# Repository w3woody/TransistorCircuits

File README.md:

# TransistorCircuits

Circuit board designs for the "Introduction to Digital Computers" series.

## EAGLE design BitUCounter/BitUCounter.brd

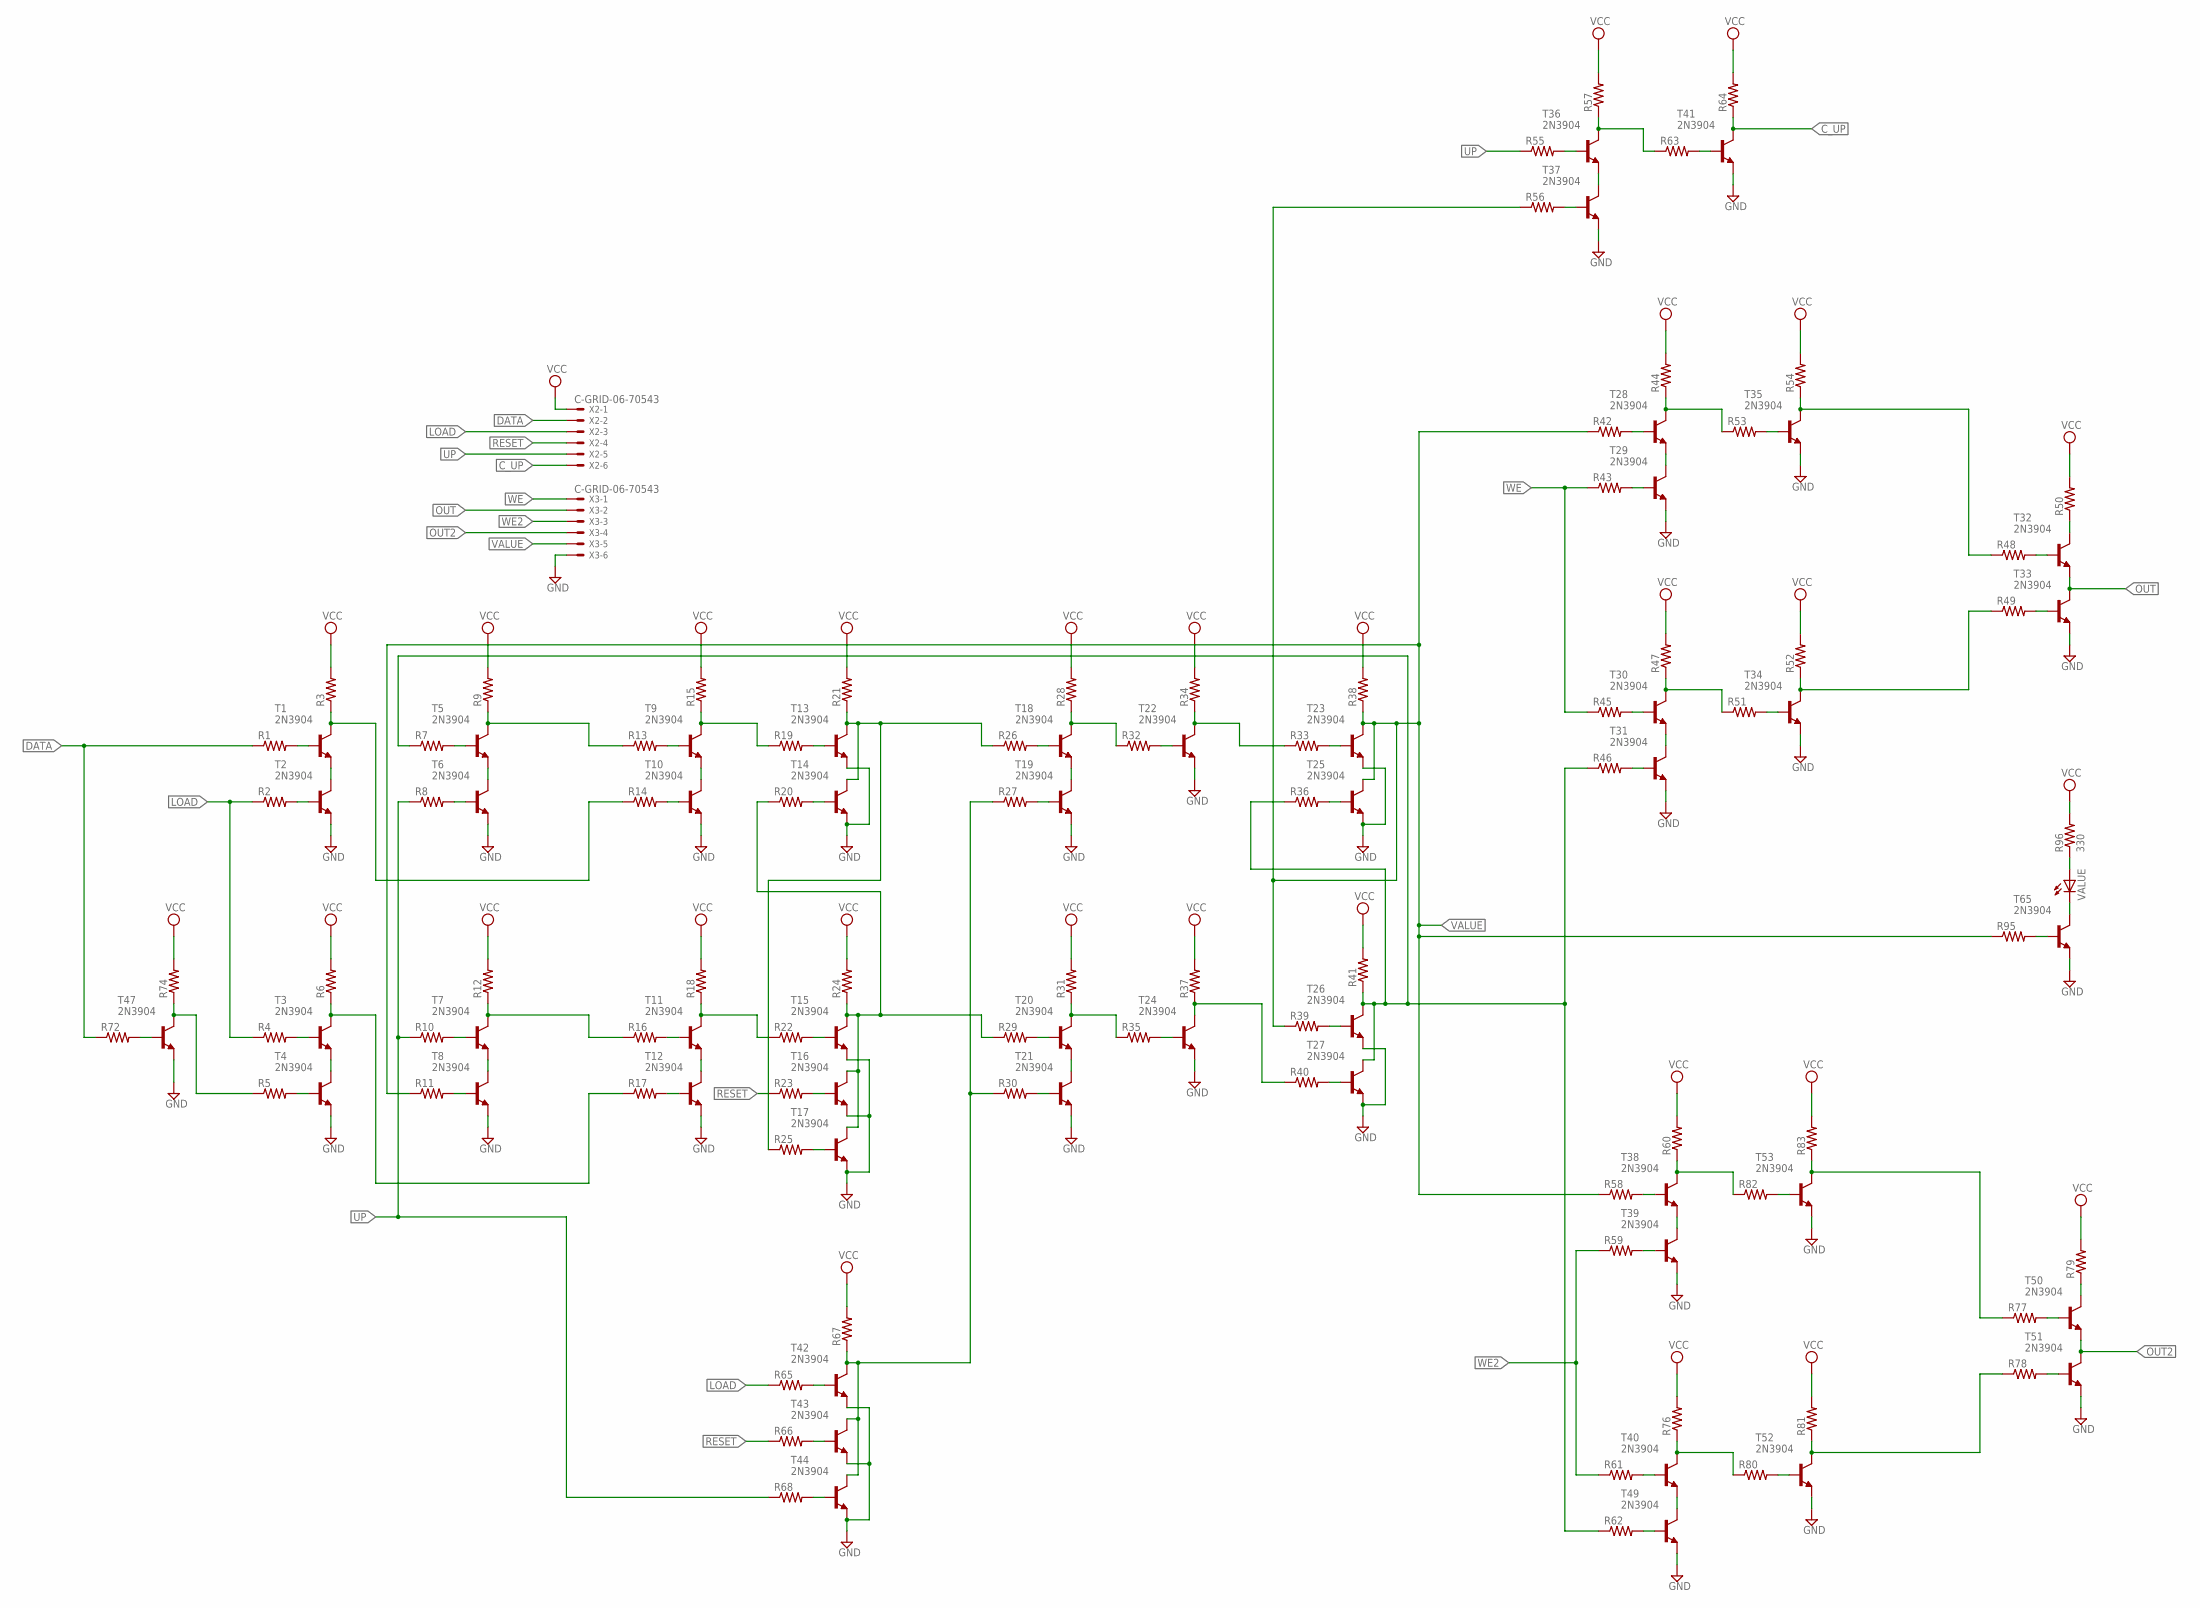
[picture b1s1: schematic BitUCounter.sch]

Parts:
R1, R2, R3, R4, R5, R6, R7, R8, R9, R10, R11, R12, R13, R14, R15, R16, R17, R18, R19, R20, R21, R22, R23, R24, R25, R26, R27, R28, R29, R30, R31, R32, R33, R34, R35, R36, R37, R38, R39, R40, R41, R42, R43, R44, R45, R46, R47, R48, R49, R50, R51, R52, R53, R54, R55, R56, R57, R58, R59, R60, R61, R62, R63, R64, R65, R66, R67, R68, R72, R74, R76, R77, R78, R79, R80, R81, R82, R83, R95: R-US_0309/10; 0309/10
R96: 330; 0309/10
T1, T2, T3, T4, T5, T6, T7, T8, T9, T10, T11, T12, T13, T14, T15, T16, T17, T18, T19, T20, T21, T22, T23, T24, T25, T26, T27, T28, T29, T30, T31, T32, T33, T34, T35, T36, T37, T38, T39, T40, T41, T42, T43, T44, T47, T49, T50, T51, T52, T53, T65: 2N3904; TO92
VALUE: LED5MM
X2, X3: C-GRID-06-70543; 70543-06

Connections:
C_UP: R64.1, T41.1 (C), X2.6
DATA: R1.1, R72.1, X2.2
GND: T2.3 (E), T4.3 (E), T6.3 (E), T8.3 (E), T10.3 (E), T12.3 (E), T13.3 (E), T14.3 (E), T15.3 (E), T16.3 (E), T17.3 (E), T19.3 (E), T21.3 (E), T22.3 (E), T23.3 (E), T24.3 (E), T25.3 (E), T26.3 (E), T27.3 (E), T29.3 (E), T31.3 (E), T33.3 (E), T34.3 (E), T35.3 (E), T37.3 (E), T39.3 (E), T41.3 (E), T42.3 (E), T43.3 (E), T44.3 (E), T47.3 (E), T49.3 (E), T51.3 (E), T52.3 (E), T53.3 (E), T65.3 (E), X3.6
LOAD: R2.1, R4.1, R65.1, X2.3
unnamed: R5.1, R74.1, T47.1 (C)
unnamed: R72.2, T47.2 (B)
unnamed: R7.1, R36.1, R41.1, R46.1, R62.1, T26.1 (C), T27.1 (C)
unnamed: R6.1, R17.1, T3.1 (C)
unnamed: T3.3 (E), T4.1 (C)
unnamed: R5.2, T4.2 (B)
unnamed: R4.2, T3.2 (B)
unnamed: R2.2, T2.2 (B)
unnamed: R1.2, T1.2 (B)
unnamed: T1.3 (E), T2.1 (C)
unnamed: R3.1, R14.1, T1.1 (C)
unnamed: R9.1, R13.1, T5.1 (C)
unnamed: R7.2, T5.2 (B)
unnamed: R8.2, T6.2 (B)
unnamed: T5.3 (E), T6.1 (C)
unnamed: R12.1, R16.1, T7.1 (C)
unnamed: R10.2, T7.2 (B)
unnamed: R11.2, T8.2 (B)
unnamed: T7.3 (E), T8.1 (C)
unnamed: R18.1, R22.1, T11.1 (C)
unnamed: R16.2, T11.2 (B)
unnamed: R17.2, T12.2 (B)
unnamed: T11.3 (E), T12.1 (C)
unnamed: R14.2, T10.2 (B)
unnamed: T9.3 (E), T10.1 (C)
unnamed: R15.1, R19.1, T9.1 (C)
unnamed: R13.2, T9.2 (B)
unnamed: R21.1, R25.1, R26.1, T13.1 (C), T14.1 (C)
unnamed: R58.2, T38.2 (B)
unnamed: R19.2, T13.2 (B)
unnamed: R20.2, T14.2 (B)
unnamed: R20.1, R24.1, R29.1, T15.1 (C), T16.1 (C), T17.1 (C)
unnamed: R59.2, T39.2 (B)
unnamed: T38.3 (E), T39.1 (C)
unnamed: R22.2, T15.2 (B)
unnamed: R23.2, T16.2 (B)
unnamed: R25.2, T17.2 (B)
unnamed: R30.2, T21.2 (B)
unnamed: T20.3 (E), T21.1 (C)
unnamed: R31.1, R35.1, T20.1 (C)
unnamed: R29.2, T20.2 (B)
unnamed: R35.2, T24.2 (B)
unnamed: R60.1, R82.1, T38.1 (C)
unnamed: R26.2, T18.2 (B)
unnamed: R27.2, T19.2 (B)
unnamed: T18.3 (E), T19.1 (C)
unnamed: R28.1, R32.1, T18.1 (C)
unnamed: R32.2, T22.2 (B)
unnamed: R33.1, R34.1, T22.1 (C)
unnamed: R82.2, T53.2 (B)
unnamed: R77.1, R83.1, T53.1 (C)
unnamed: R78.1, R81.1, T52.1 (C)
unnamed: R36.2, T25.2 (B)
unnamed: R33.2, T23.2 (B)
unnamed: R80.2, T52.2 (B)
unnamed: R39.2, T26.2 (B)
unnamed: R40.2, T27.2 (B)
unnamed: R42.2, T28.2 (B)
unnamed: R43.2, T29.2 (B)
unnamed: T28.3 (E), T29.1 (C)
unnamed: R44.1, R53.1, T28.1 (C)
unnamed: R53.2, T35.2 (B)
unnamed: R48.1, R54.1, T35.1 (C)
unnamed: R49.1, R52.1, T34.1 (C)
unnamed: R51.2, T34.2 (B)
unnamed: R47.1, R51.1, T30.1 (C)
unnamed: T30.3 (E), T31.1 (C)
unnamed: R46.2, T31.2 (B)
unnamed: R45.2, T30.2 (B)
unnamed: R48.2, T32.2 (B)
unnamed: R50.1, T32.1 (C)
unnamed: R76.1, R80.1, T40.1 (C)
unnamed: R49.2, T33.2 (B)
unnamed: T40.3 (E), T49.1 (C)
unnamed: R62.2, T49.2 (B)
unnamed: R61.2, T40.2 (B)
unnamed: R77.2, T50.2 (B)
unnamed: R57.1, R63.1, T36.1 (C)
unnamed: T36.3 (E), T37.1 (C)
unnamed: R56.2, T37.2 (B)
unnamed: R55.2, T36.2 (B)
unnamed: R79.1, T50.1 (C)
unnamed: R63.2, T41.2 (B)
unnamed: R78.2, T51.2 (B)
unnamed: R65.2, T42.2 (B)
unnamed: R66.2, T43.2 (B)
unnamed: R68.2, T44.2 (B)
unnamed: R27.1, R30.1, R67.1, T42.1 (C), T43.1 (C), T44.1 (C)
unnamed: R37.1, R40.1, T24.1 (C)
unnamed: R96.1, VALUE.A
unnamed: R95.2, T65.2 (B)
unnamed: T65.1 (C), VALUE.K (C)
OUT: T32.3 (E), T33.1 (C), X3.2
OUT2: T50.3 (E), T51.1 (C), X3.4
RESET: R23.1, R66.1, X2.4
UP: R8.1, R10.1, R55.1, R68.1, X2.5
VALUE: R11.1, R38.1, R39.1, R42.1, R56.1, R58.1, R95.1, T23.1 (C), T25.1 (C), X3.5
VCC: R3.2, R6.2, R9.2, R12.2, R15.2, R18.2, R21.2, R24.2, R28.2, R31.2, R34.2, R37.2, R38.2, R41.2, R44.2, R47.2, R50.2, R52.2, R54.2, R57.2, R60.2, R64.2, R67.2, R74.2, R76.2, R79.2, R81.2, R83.2, R96.2, X2.1
WE: R43.1, R45.1, X3.1
WE2: R59.1, R61.1, X3.3

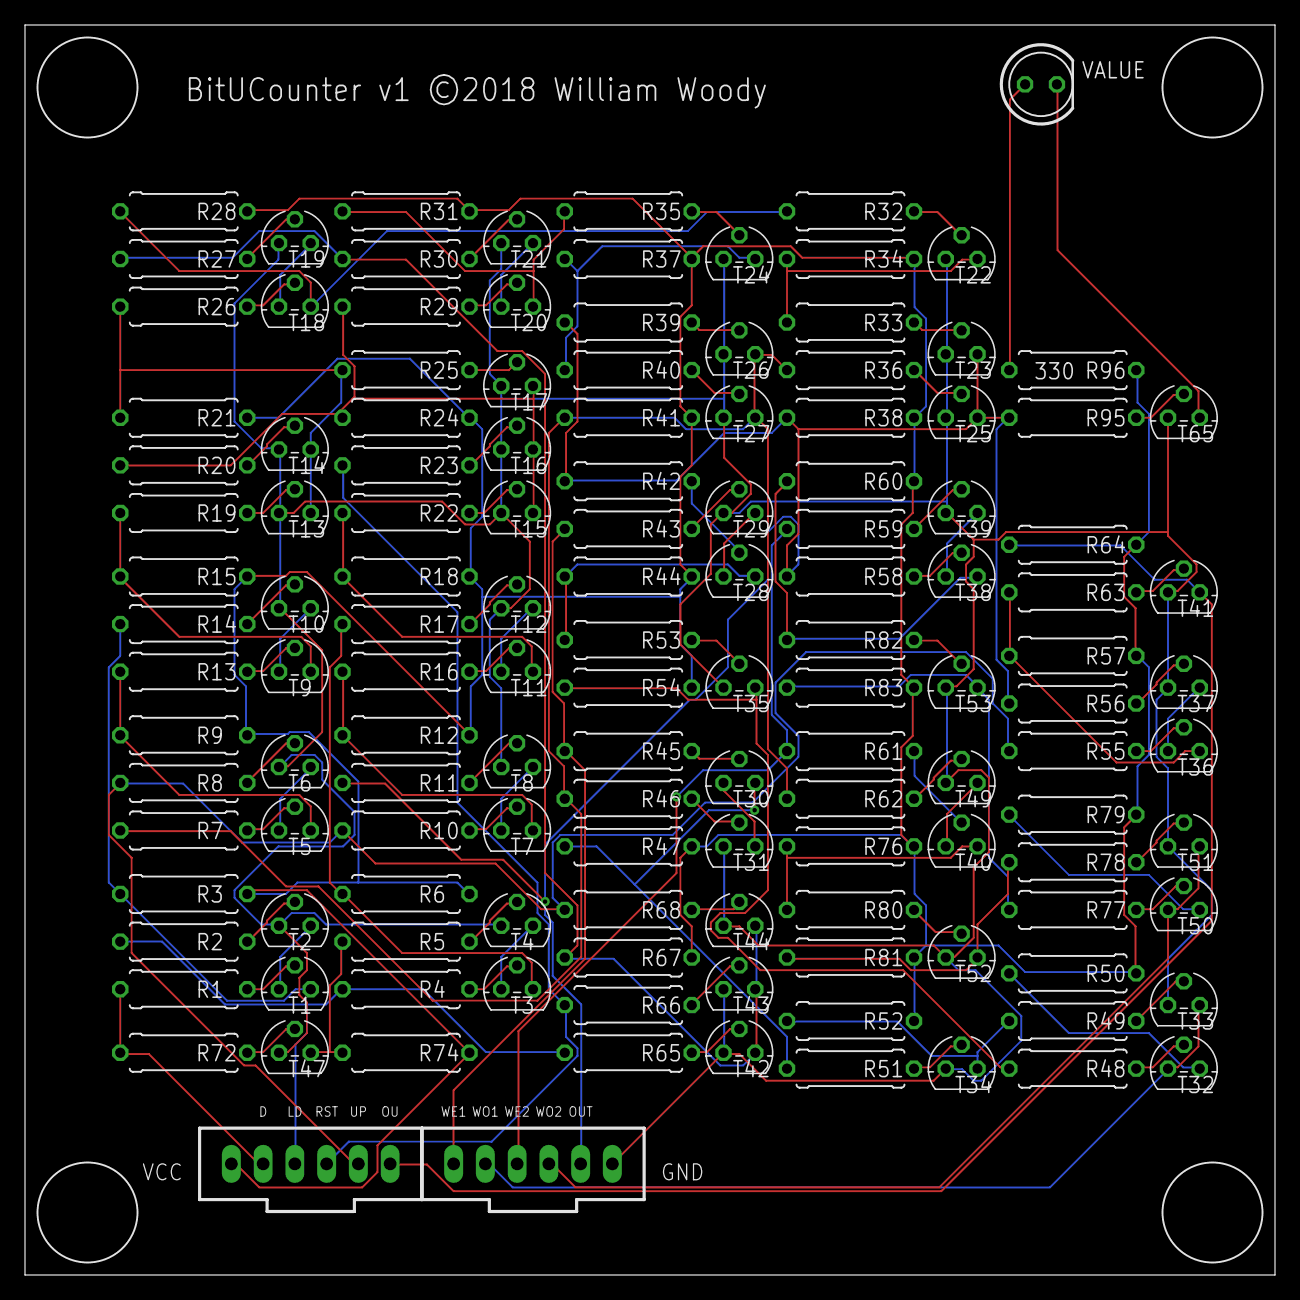
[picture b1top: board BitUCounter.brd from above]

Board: 2 copper layers, 100.0 x 100.0 mm, 134 parts (0 on the bottom side), 104 nets.

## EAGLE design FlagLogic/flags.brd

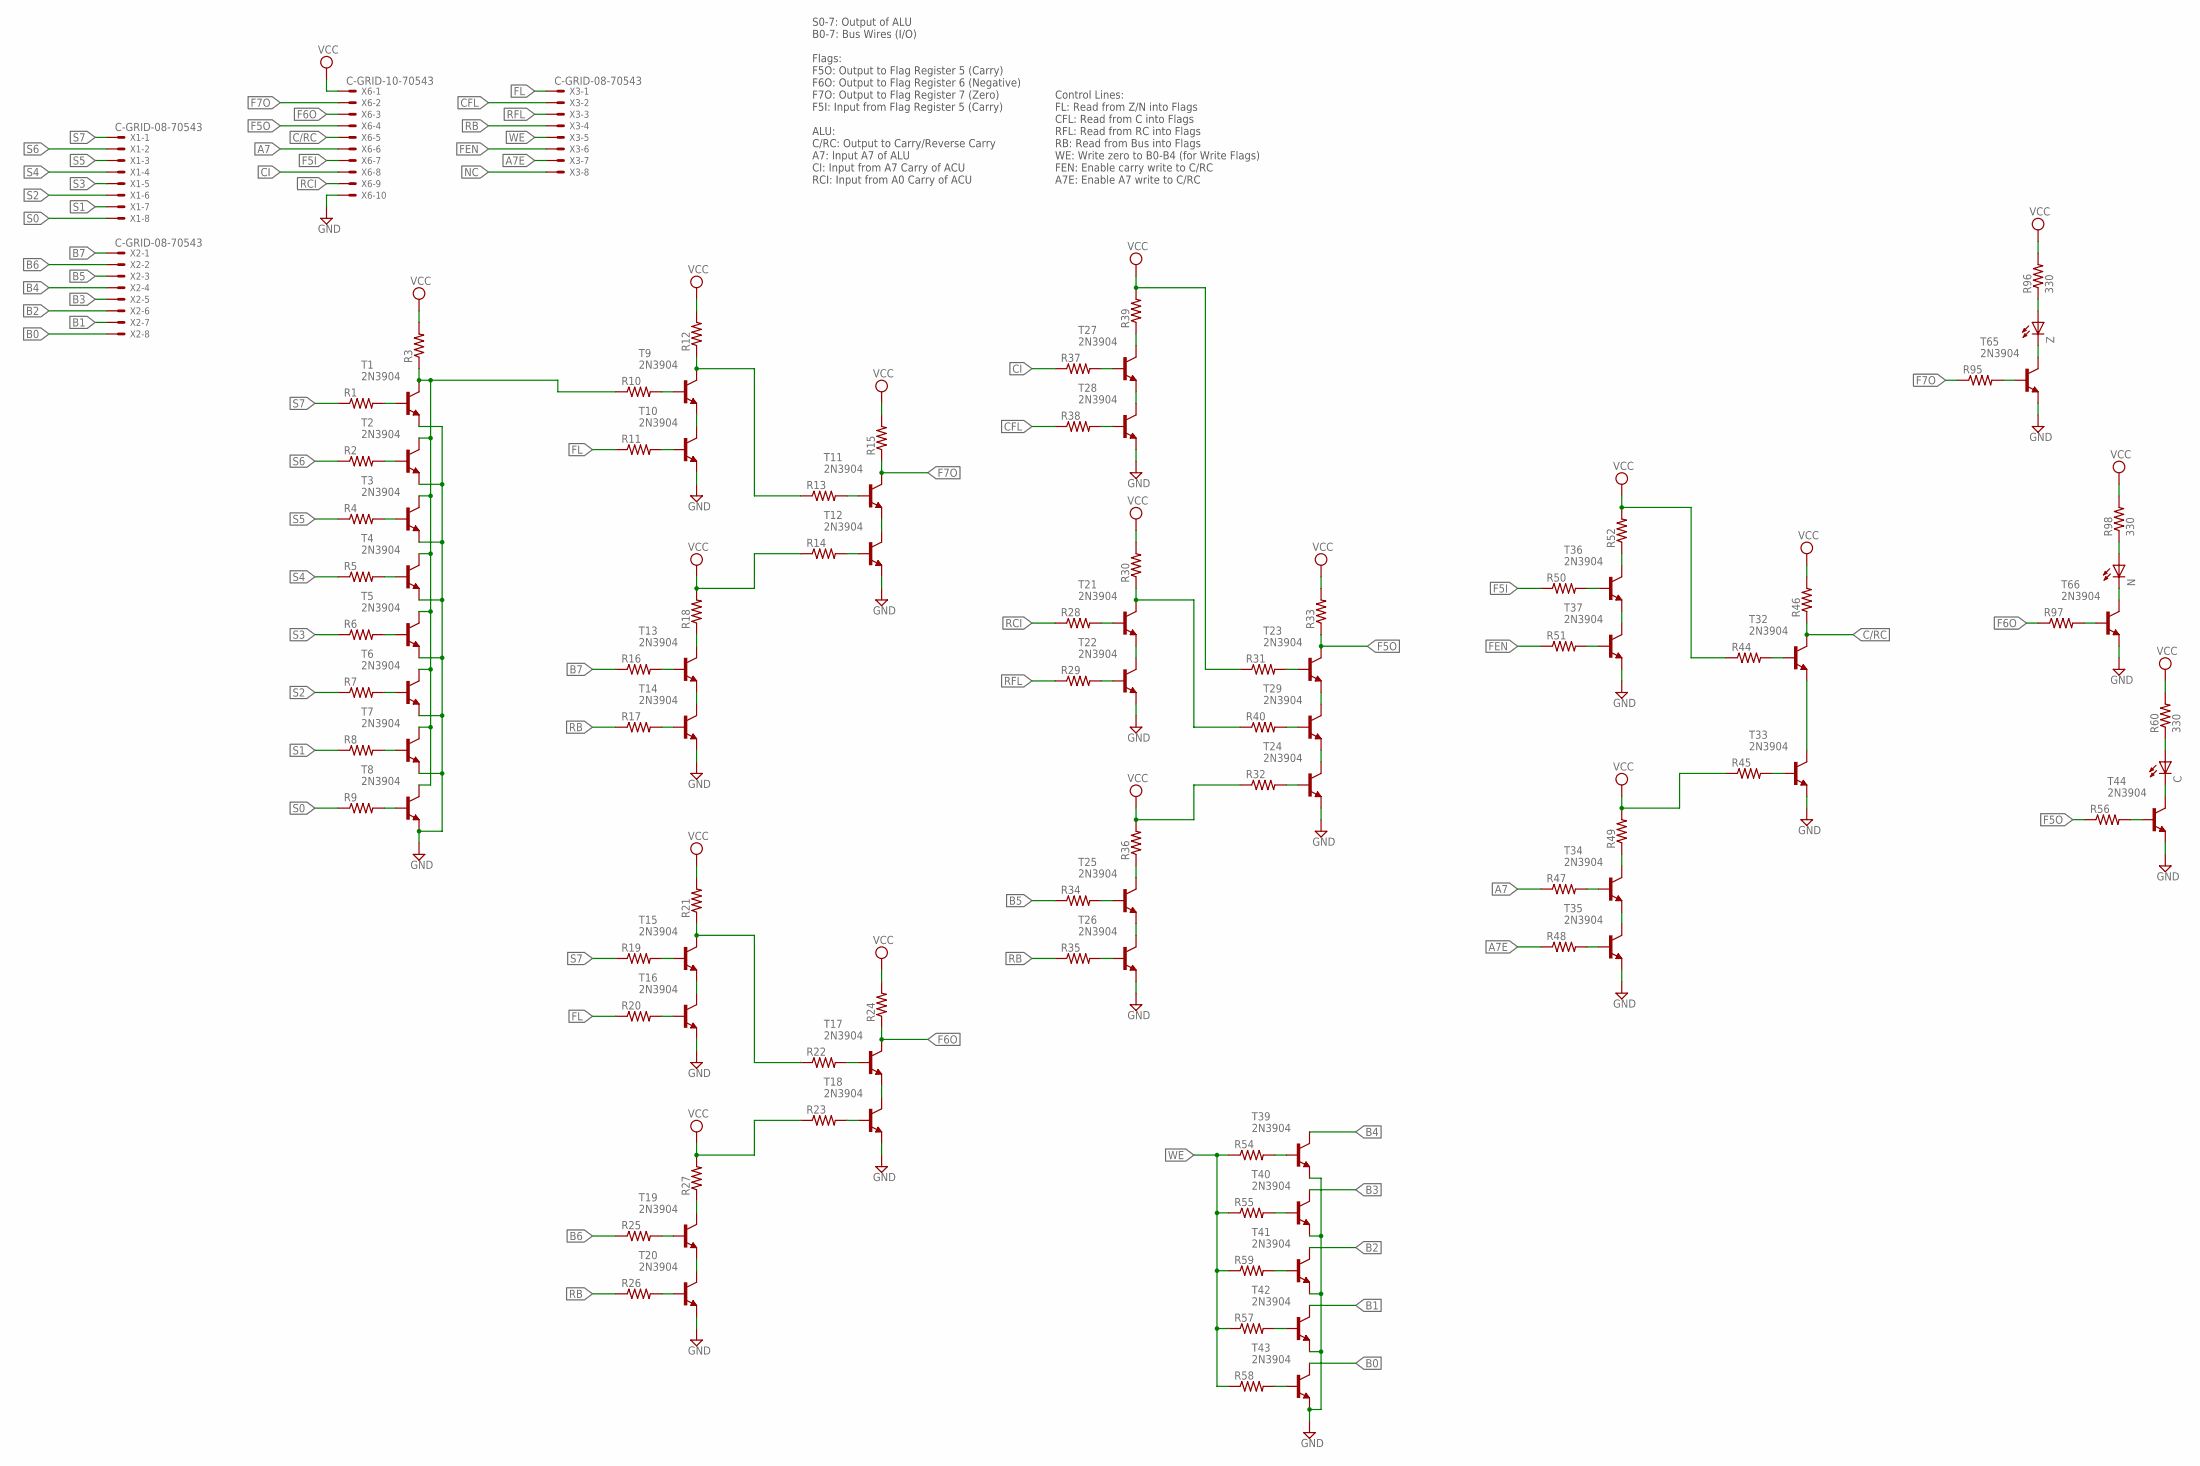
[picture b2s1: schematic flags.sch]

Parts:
C: LED5MM
N: LED5MM
R1, R2, R3, R4, R5, R6, R7, R8, R9, R10, R11, R12, R13, R14, R15, R16, R17, R18, R19, R20, R21, R22, R23, R24, R25, R26, R27, R28, R29, R30, R31, R32, R33, R34, R35, R36, R37, R38, R39, R40, R44, R45, R46, R47, R48, R49, R50, R51, R52, R54, R55, R56, R57, R58, R59, R95, R97: R-US_0309/10; 0309/10
R60, R96, R98: 330; 0309/10
T1, T2, T3, T4, T5, T6, T7, T8, T9, T10, T11, T12, T13, T14, T15, T16, T17, T18, T19, T20, T21, T22, T23, T24, T25, T26, T27, T28, T29, T32, T33, T34, T35, T36, T37, T39, T40, T41, T42, T43, T44, T65, T66: 2N3904; TO92
X1, X2, X3: C-GRID-08-70543; 70543-08
X6: C-GRID-10-70543; 70543-10
Z: LED5MM

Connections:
A7: R47.1, X6.6
A7E: R48.1, X3.7
B0: T43.1 (C), X2.8
B1: T42.1 (C), X2.7
B2: T41.1 (C), X2.6
B3: T40.1 (C), X2.5
B4: T39.1 (C), X2.4
B5: R34.1, X2.3
B6: R25.1, X2.2
B7: R16.1, X2.1
C/RC: R46.1, T32.1 (C), X6.5
CFL: R38.1, X3.2
CI: R37.1, X6.8
F5I: R50.1, X6.7
F5O: R33.1, R56.1, T23.1 (C), X6.4
F6O: R24.1, R97.1, T17.1 (C), X6.3
F7O: R15.1, R95.1, T11.1 (C), X6.2
FEN: R51.1, X3.6
FL: R11.1, R20.1, X3.1
GND: T1.3 (E), T2.3 (E), T3.3 (E), T4.3 (E), T5.3 (E), T6.3 (E), T7.3 (E), T8.3 (E), T10.3 (E), T12.3 (E), T14.3 (E), T16.3 (E), T18.3 (E), T20.3 (E), T22.3 (E), T24.3 (E), T26.3 (E), T28.3 (E), T33.3 (E), T35.3 (E), T37.3 (E), T39.3 (E), T40.3 (E), T41.3 (E), T42.3 (E), T43.3 (E), T44.3 (E), T65.3 (E), T66.3 (E), X6.10
unnamed: R3.1, R10.1, T1.1 (C), T2.1 (C), T3.1 (C), T4.1 (C), T5.1 (C), T6.1 (C), T7.1 (C), T8.1 (C)
unnamed: R1.2, T1.2 (B)
unnamed: R2.2, T2.2 (B)
unnamed: R4.2, T3.2 (B)
unnamed: R5.2, T4.2 (B)
unnamed: R6.2, T5.2 (B)
unnamed: R7.2, T6.2 (B)
unnamed: R8.2, T7.2 (B)
unnamed: R9.2, T8.2 (B)
unnamed: R30.1, R40.1, T21.1 (C)
unnamed: R12.1, R13.1, T9.1 (C)
unnamed: T9.3 (E), T10.1 (C)
unnamed: R11.2, T10.2 (B)
unnamed: R10.2, T9.2 (B)
unnamed: R21.1, R22.1, T15.1 (C)
unnamed: T15.3 (E), T16.1 (C)
unnamed: R20.2, T16.2 (B)
unnamed: R19.2, T15.2 (B)
unnamed: R18.1, T13.1 (C)
unnamed: R16.2, T13.2 (B)
unnamed: R17.2, T14.2 (B)
unnamed: T13.3 (E), T14.1 (C)
unnamed: R27.1, T19.1 (C)
unnamed: R14.2, T12.2 (B)
unnamed: T11.3 (E), T12.1 (C)
unnamed: R13.2, T11.2 (B)
unnamed: R25.2, T19.2 (B)
unnamed: R26.2, T20.2 (B)
unnamed: T19.3 (E), T20.1 (C)
unnamed: R23.2, T18.2 (B)
unnamed: T17.3 (E), T18.1 (C)
unnamed: R22.2, T17.2 (B)
unnamed: T21.3 (E), T22.1 (C)
unnamed: R29.2, T22.2 (B)
unnamed: R28.2, T21.2 (B)
unnamed: R36.1, T25.1 (C)
unnamed: R34.2, T25.2 (B)
unnamed: R35.2, T26.2 (B)
unnamed: T25.3 (E), T26.1 (C)
unnamed: R32.2, T24.2 (B)
unnamed: T23.3 (E), T29.1 (C)
unnamed: R31.2, T23.2 (B)
unnamed: R39.1, T27.1 (C)
unnamed: R37.2, T27.2 (B)
unnamed: R38.2, T28.2 (B)
unnamed: T27.3 (E), T28.1 (C)
unnamed: T24.1 (C), T29.3 (E)
unnamed: R40.2, T29.2 (B)
unnamed: R49.1, T34.1 (C)
unnamed: R47.2, T34.2 (B)
unnamed: R48.2, T35.2 (B)
unnamed: T34.3 (E), T35.1 (C)
unnamed: R45.2, T33.2 (B)
unnamed: R44.2, T32.2 (B)
unnamed: R52.1, T36.1 (C)
unnamed: R50.2, T36.2 (B)
unnamed: R51.2, T37.2 (B)
unnamed: T36.3 (E), T37.1 (C)
unnamed: T32.3 (E), T33.1 (C)
unnamed: R56.2, T44.2 (B)
unnamed: R54.2, T39.2 (B)
unnamed: R55.2, T40.2 (B)
unnamed: R59.2, T41.2 (B)
unnamed: R57.2, T42.2 (B)
unnamed: R58.2, T43.2 (B)
unnamed: C.A, R60.1
unnamed: C.K (C), T44.1 (C)
unnamed: R96.1, Z.A
unnamed: R95.2, T65.2 (B)
unnamed: R97.2, T66.2 (B)
unnamed: T65.1 (C), Z.K (C)
unnamed: N.A, R98.1
unnamed: N.K (C), T66.1 (C)
NC: X3.8
RB: R17.1, R26.1, R35.1, X3.4
RCI: R28.1, X6.9
RFL: R29.1, X3.3
S0: R9.1, X1.8
S1: R8.1, X1.7
S2: R7.1, X1.6
S3: R6.1, X1.5
S4: R5.1, X1.4
S5: R4.1, X1.3
S6: R2.1, X1.2
S7: R1.1, R19.1, X1.1
VCC: R3.2, R12.2, R14.1, R15.2, R18.2, R21.2, R23.1, R24.2, R27.2, R30.2, R31.1, R32.1, R33.2, R36.2, R39.2, R44.1, R45.1, R46.2, R49.2, R52.2, R60.2, R96.2, R98.2, X6.1
WE: R54.1, R55.1, R57.1, R58.1, R59.1, X3.5

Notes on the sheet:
S0-7: Output of ALU B0-7: Bus Wires (I/O) Flags: F5O: Output to Flag Register 5 (Carry) F6O: Output to Flag Register 6 (Negative) F7O: Output to Flag Register 7 (Zero) F5I: Input from Flag Register 5 (Carry) ALU: C/RC: Output to Carry/Reverse Carry A7: Input A7 of ALU CI: Input from A7 Carry of ACU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
Control Lines: FL: Read from Z/N into Flags CFL: Read from C into Flags RFL: Read from RC into Flags RB: Read from Bus into Flags WE: Write zero to B0-B4 (for Write Flags) FEN: Enable carry write to C/RC A7E: Enable A7 write to C/RC

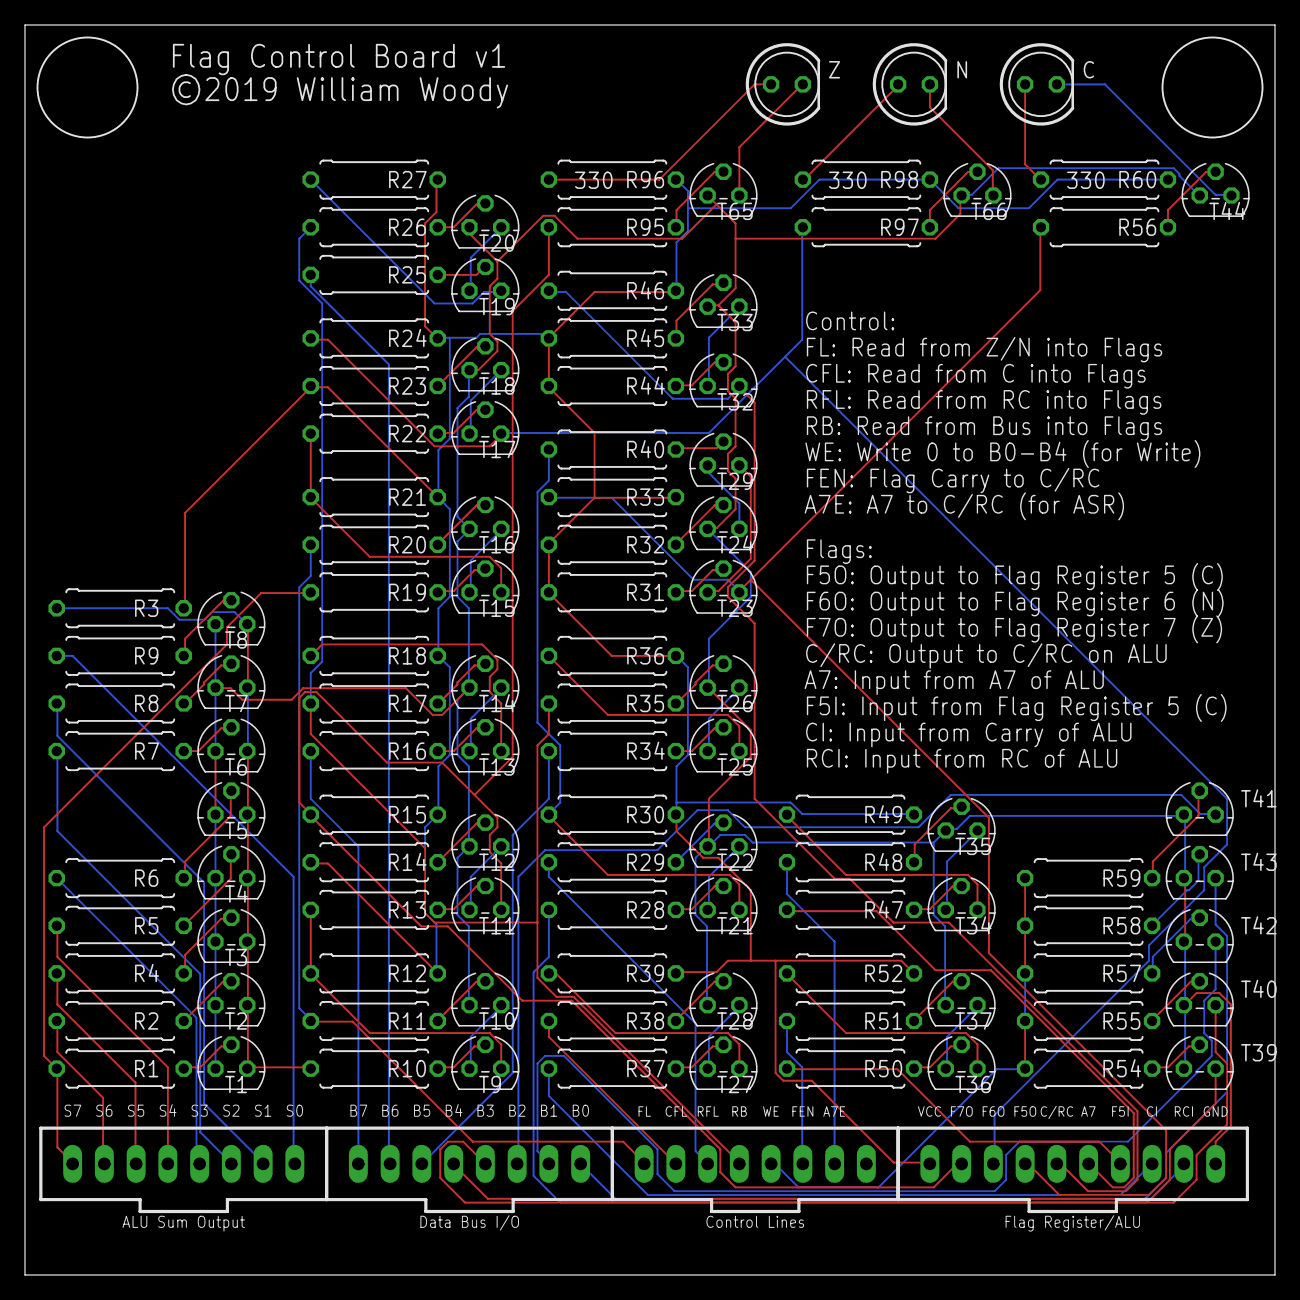
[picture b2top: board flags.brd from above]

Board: 2 copper layers, 100.0 x 100.0 mm, 110 parts (0 on the bottom side), 106 nets.

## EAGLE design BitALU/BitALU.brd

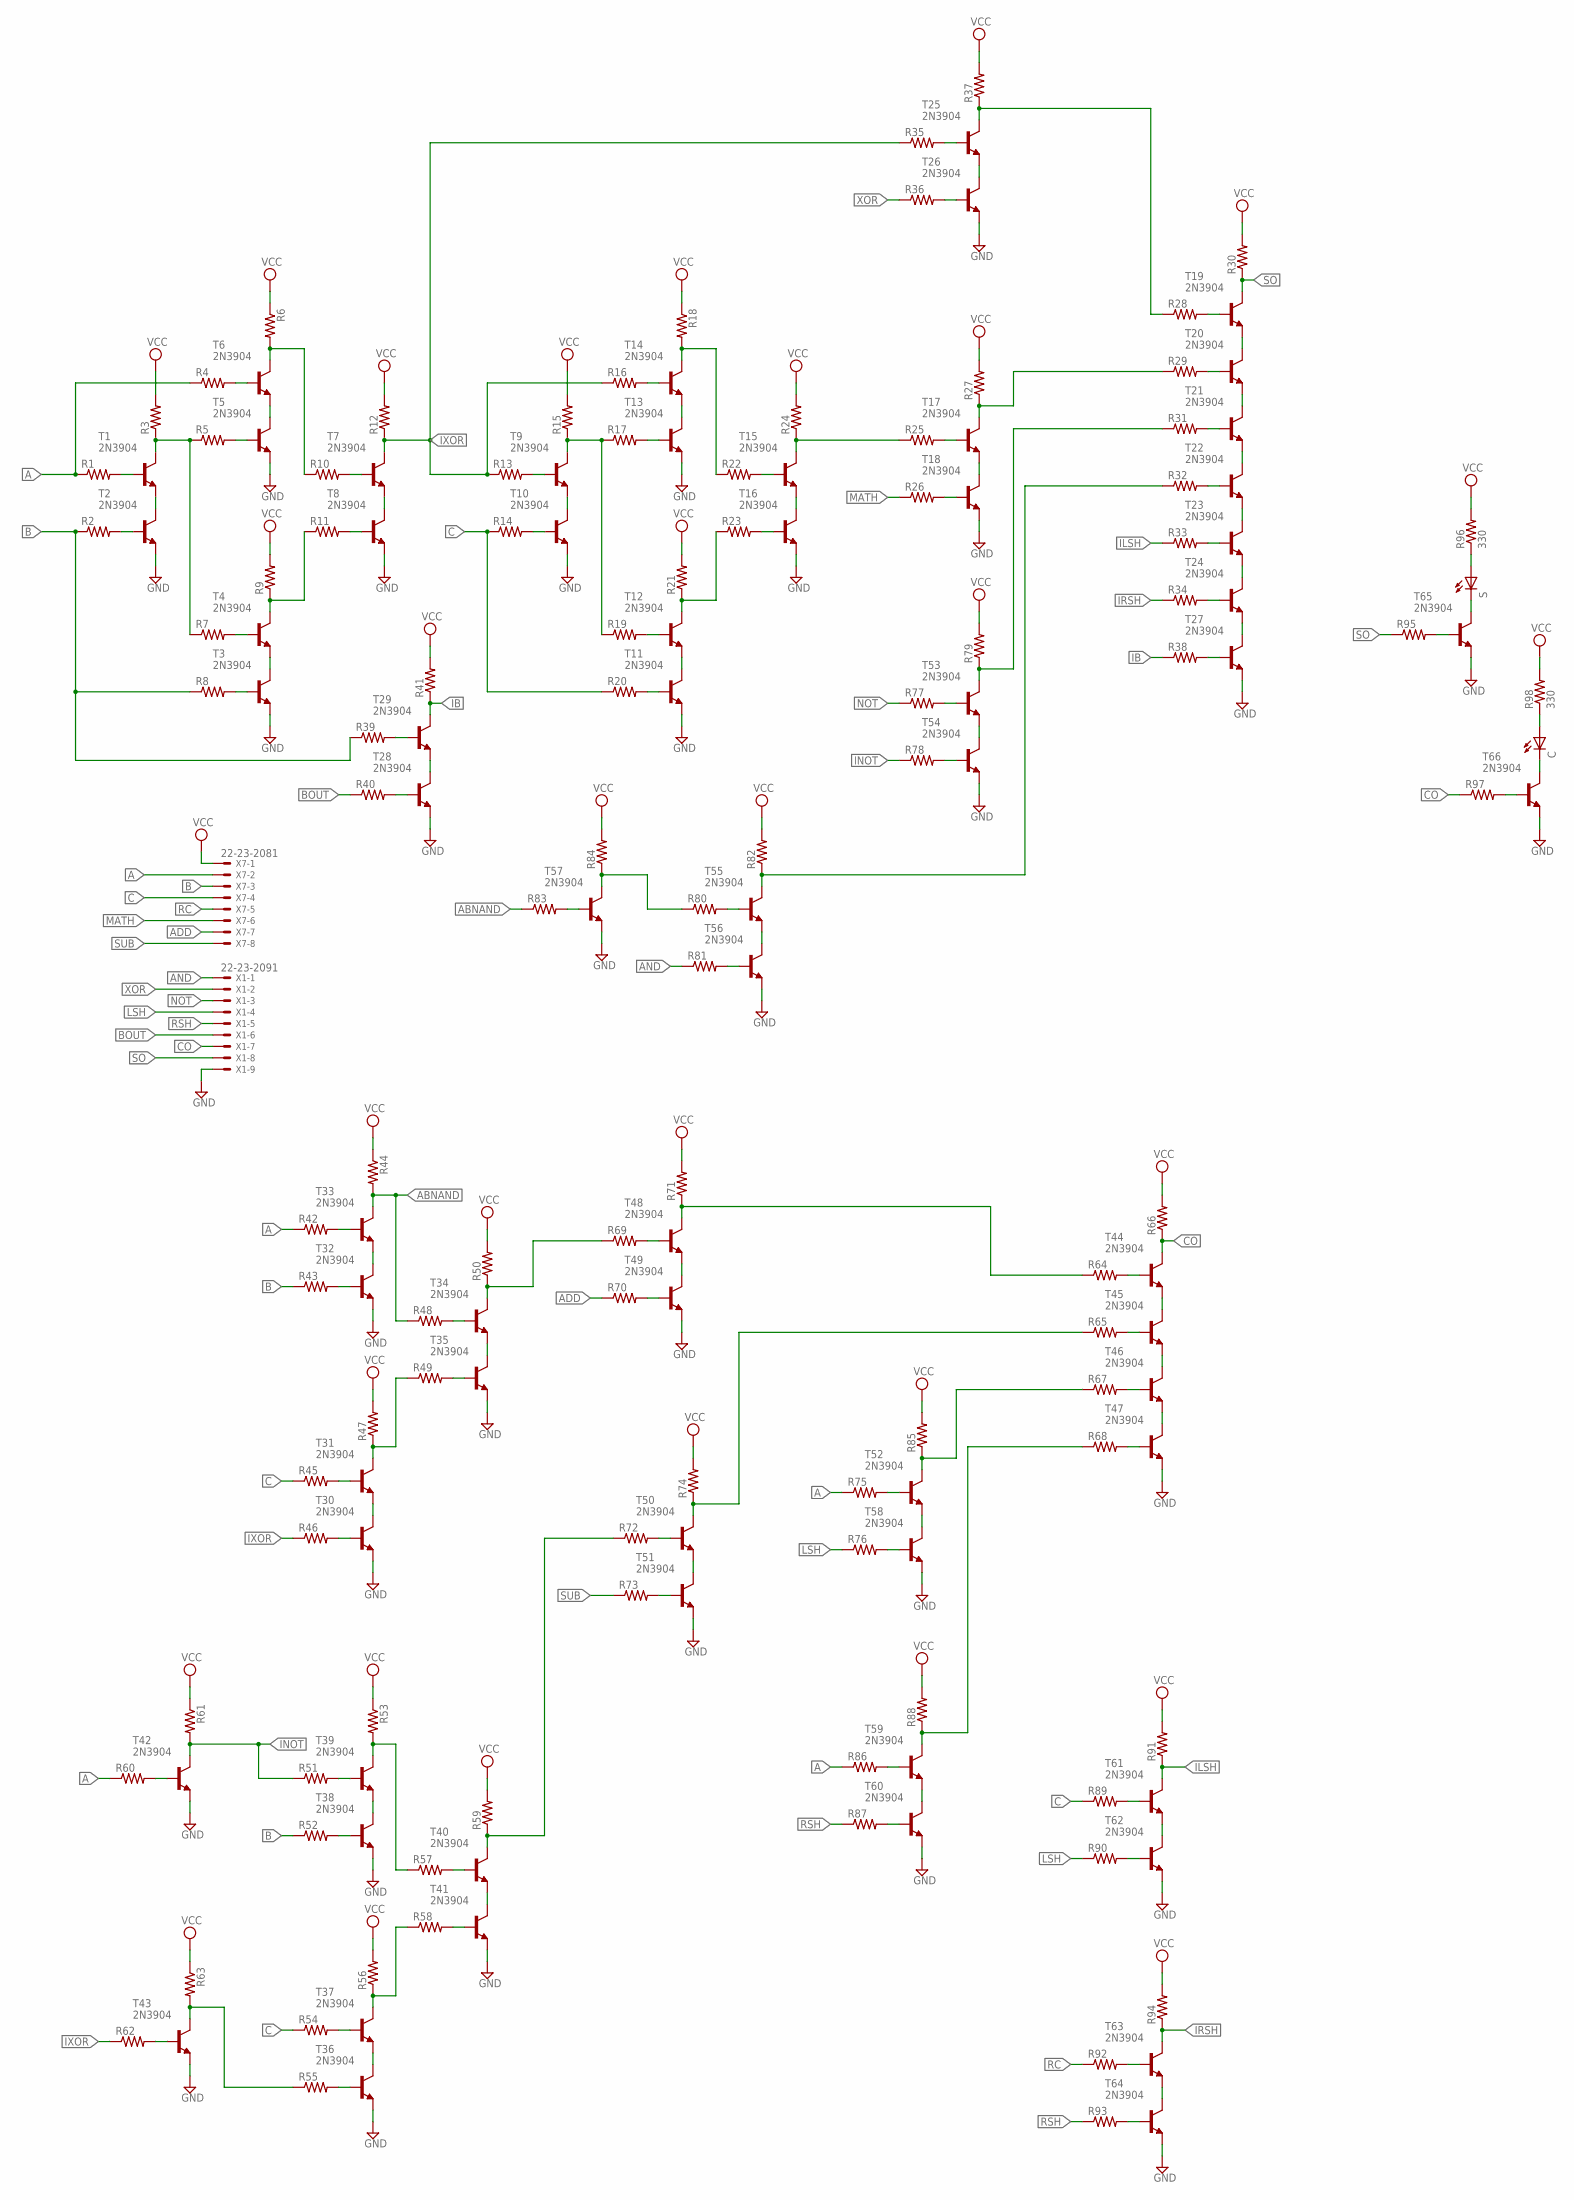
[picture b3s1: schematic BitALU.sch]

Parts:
C: LED5MM
R1, R2, R3, R4, R5, R6, R7, R8, R9, R10, R11, R12, R13, R14, R15, R16, R17, R18, R19, R20, R21, R22, R23, R24, R25, R26, R27, R28, R29, R30, R31, R32, R33, R34, R35, R36, R37, R38, R39, R40, R41, R42, R43, R44, R45, R46, R47, R48, R49, R50, R51, R52, R53, R54, R55, R56, R57, R58, R59, R60, R61, R62, R63, R64, R65, R66, R67, R68, R69, R70, R71, R72, R73, R74, R75, R76, R77, R78, R79, R80, R81, R82, R83, R84, R85, R86, R87, R88, R89, R90, R91, R92, R93, R94, R95, R97: R-US_0309/10; 0309/10
R96, R98: 330; 0309/10
S: LED5MM
T1, T2, T3, T4, T5, T6, T7, T8, T9, T10, T11, T12, T13, T14, T15, T16, T17, T18, T19, T20, T21, T22, T23, T24, T25, T26, T27, T28, T29, T30, T31, T32, T33, T34, T35, T36, T37, T38, T39, T40, T41, T42, T43, T44, T45, T46, T47, T48, T49, T50, T51, T52, T53, T54, T55, T56, T57, T58, T59, T60, T61, T62, T63, T64, T65, T66: 2N3904; TO92
X1: 22-23-2091
X7: 22-23-2081

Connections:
A: R1.1, R4.1, R42.1, R60.1, R75.1, R86.1, X7.2
ABNAND: R44.2, R48.1, R83.1, T33.1 (C)
ADD: R70.1, X7.7
AND: R81.1, X1.1
B: R2.1, R8.1, R39.1, R43.1, R52.1, X7.3
BOUT: R40.1, X1.6
C: R14.1, R20.1, R45.1, R54.1, R89.1, X7.4
CO: R66.1, R97.1, T44.1 (C), X1.7
GND: T2.3 (E), T3.3 (E), T5.3 (E), T8.3 (E), T10.3 (E), T11.3 (E), T13.3 (E), T16.3 (E), T18.3 (E), T26.3 (E), T27.3 (E), T28.3 (E), T30.3 (E), T32.3 (E), T35.3 (E), T36.3 (E), T38.3 (E), T41.3 (E), T42.3 (E), T43.3 (E), T47.3 (E), T49.3 (E), T51.3 (E), T54.3 (E), T56.3 (E), T57.3 (E), T58.3 (E), T60.3 (E), T62.3 (E), T64.3 (E), T65.3 (E), T66.3 (E), X1.9
IB: R38.1, R41.1, T29.1 (C)
ILSH: R33.1, R91.1, T61.1 (C)
INOT: R51.1, R61.2, R78.1, T42.1 (C)
IRSH: R34.1, R94.1, T63.1 (C)
IXOR: R12.1, R13.1, R16.1, R35.1, R46.1, R62.1, T7.1 (C)
LSH: R76.1, R90.1, X1.4
MATH: R26.1, X7.6
unnamed: R3.1, R5.1, R7.1, T1.1 (C)
unnamed: T1.3 (E), T2.1 (C)
unnamed: R2.2, T2.2 (B)
unnamed: R1.2, T1.2 (B)
unnamed: R5.2, T5.2 (B)
unnamed: R7.2, T4.2 (B)
unnamed: R4.2, T6.2 (B)
unnamed: R6.2, R10.1, T6.1 (C)
unnamed: T5.1 (C), T6.3 (E)
unnamed: R9.1, R11.1, T4.1 (C)
unnamed: T3.1 (C), T4.3 (E)
unnamed: R10.2, T7.2 (B)
unnamed: R11.2, T8.2 (B)
unnamed: R28.1, R37.1, T25.1 (C)
unnamed: R15.1, R17.1, R19.1, T9.1 (C)
unnamed: R8.2, T3.2 (B)
unnamed: T19.3 (E), T20.1 (C)
unnamed: T7.3 (E), T8.1 (C)
unnamed: T9.3 (E), T10.1 (C)
unnamed: R14.2, T10.2 (B)
unnamed: R13.2, T9.2 (B)
unnamed: R17.2, T13.2 (B)
unnamed: R19.2, T12.2 (B)
unnamed: R16.2, T14.2 (B)
unnamed: R18.2, R22.1, T14.1 (C)
unnamed: T13.1 (C), T14.3 (E)
unnamed: R21.1, R23.1, T12.1 (C)
unnamed: T11.1 (C), T12.3 (E)
unnamed: R22.2, T15.2 (B)
unnamed: R23.2, T16.2 (B)
unnamed: R24.1, R25.1, T15.1 (C)
unnamed: R20.2, T11.2 (B)
unnamed: R25.2, T17.2 (B)
unnamed: T15.3 (E), T16.1 (C)
unnamed: R26.2, T18.2 (B)
unnamed: R27.1, R29.1, T17.1 (C)
unnamed: T17.3 (E), T18.1 (C)
unnamed: T20.3 (E), T21.1 (C)
unnamed: T21.3 (E), T22.1 (C)
unnamed: T22.3 (E), T23.1 (C)
unnamed: T23.3 (E), T24.1 (C)
unnamed: R28.2, T19.2 (B)
unnamed: T25.3 (E), T26.1 (C)
unnamed: R36.2, T26.2 (B)
unnamed: R35.2, T25.2 (B)
unnamed: R29.2, T20.2 (B)
unnamed: R31.2, T21.2 (B)
unnamed: R32.2, T22.2 (B)
unnamed: R33.2, T23.2 (B)
unnamed: R34.2, T24.2 (B)
unnamed: T24.3 (E), T27.1 (C)
unnamed: R38.2, T27.2 (B)
unnamed: T32.1 (C), T33.3 (E)
unnamed: T28.1 (C), T29.3 (E)
unnamed: R39.2, T29.2 (B)
unnamed: R40.2, T28.2 (B)
unnamed: R43.2, T32.2 (B)
unnamed: R42.2, T33.2 (B)
unnamed: R50.1, R69.1, T34.1 (C)
unnamed: T34.3 (E), T35.1 (C)
unnamed: R49.2, T35.2 (B)
unnamed: R48.2, T34.2 (B)
unnamed: R47.1, R49.1, T31.1 (C)
unnamed: T30.1 (C), T31.3 (E)
unnamed: R46.2, T30.2 (B)
unnamed: R45.2, T31.2 (B)
unnamed: T44.3 (E), T45.1 (C)
unnamed: T45.3 (E), T46.1 (C)
unnamed: T46.3 (E), T47.1 (C)
unnamed: R68.2, T47.2 (B)
unnamed: R67.2, T46.2 (B)
unnamed: R65.2, T45.2 (B)
unnamed: R64.2, T44.2 (B)
unnamed: R64.1, R71.1, T48.1 (C)
unnamed: R31.1, R79.1, T53.1 (C)
unnamed: T48.3 (E), T49.1 (C)
unnamed: R70.2, T49.2 (B)
unnamed: R69.2, T48.2 (B)
unnamed: R65.1, R74.1, T50.1 (C)
unnamed: T50.3 (E), T51.1 (C)
unnamed: R73.2, T51.2 (B)
unnamed: R72.2, T50.2 (B)
unnamed: R60.2, T42.2 (B)
unnamed: R53.2, R57.1, T39.1 (C)
unnamed: T38.1 (C), T39.3 (E)
unnamed: R52.2, T38.2 (B)
unnamed: R51.2, T39.2 (B)
unnamed: R56.1, R58.1, T37.1 (C)
unnamed: T36.1 (C), T37.3 (E)
unnamed: R55.2, T36.2 (B)
unnamed: R54.2, T37.2 (B)
unnamed: R59.1, R72.1, T40.1 (C)
unnamed: T40.3 (E), T41.1 (C)
unnamed: R58.2, T41.2 (B)
unnamed: R57.2, T40.2 (B)
unnamed: R55.1, R63.2, T43.1 (C)
unnamed: R62.2, T43.2 (B)
unnamed: R67.1, R85.1, T52.1 (C)
unnamed: T52.3 (E), T58.1 (C)
unnamed: R76.2, T58.2 (B)
unnamed: R75.2, T52.2 (B)
unnamed: R68.1, R88.1, T59.1 (C)
unnamed: T53.3 (E), T54.1 (C)
unnamed: R78.2, T54.2 (B)
unnamed: R77.2, T53.2 (B)
unnamed: R83.2, T57.2 (B)
unnamed: R80.1, R84.1, T57.1 (C)
unnamed: T59.3 (E), T60.1 (C)
unnamed: R87.2, T60.2 (B)
unnamed: R80.2, T55.2 (B)
unnamed: R32.1, R82.1, T55.1 (C)
unnamed: T55.3 (E), T56.1 (C)
unnamed: R81.2, T56.2 (B)
unnamed: R86.2, T59.2 (B)
unnamed: T61.3 (E), T62.1 (C)
unnamed: R90.2, T62.2 (B)
unnamed: R89.2, T61.2 (B)
unnamed: T63.3 (E), T64.1 (C)
unnamed: R93.2, T64.2 (B)
unnamed: R92.2, T63.2 (B)
unnamed: R96.1, S.A
unnamed: R95.2, T65.2 (B)
unnamed: R97.2, T66.2 (B)
unnamed: S.K (C), T65.1 (C)
unnamed: C.A, R98.1
unnamed: C.K (C), T66.1 (C)
NOT: R77.1, X1.3
RC: R92.1, X7.5
RSH: R87.1, R93.1, X1.5
SO: R30.1, R95.1, T19.1 (C), X1.8
SUB: R73.1, X7.8
VCC: R3.2, R6.1, R9.2, R12.2, R15.2, R18.1, R21.2, R24.2, R27.2, R30.2, R37.2, R41.2, R44.1, R47.2, R50.2, R53.1, R56.2, R59.2, R61.1, R63.1, R66.2, R71.2, R74.2, R79.2, R82.2, R84.2, R85.2, R88.2, R91.2, R94.2, R96.2, R98.2, X7.1
XOR: R36.1, X1.2

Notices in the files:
BitALU/BitALU.brd:
ALU v2 ©2018 William Woody
BitUCounter/BitUCounter.brd:
BitUCounter v1 ©2018 William Woody
FlagLogic/flags.brd:
©2019 William Woody
